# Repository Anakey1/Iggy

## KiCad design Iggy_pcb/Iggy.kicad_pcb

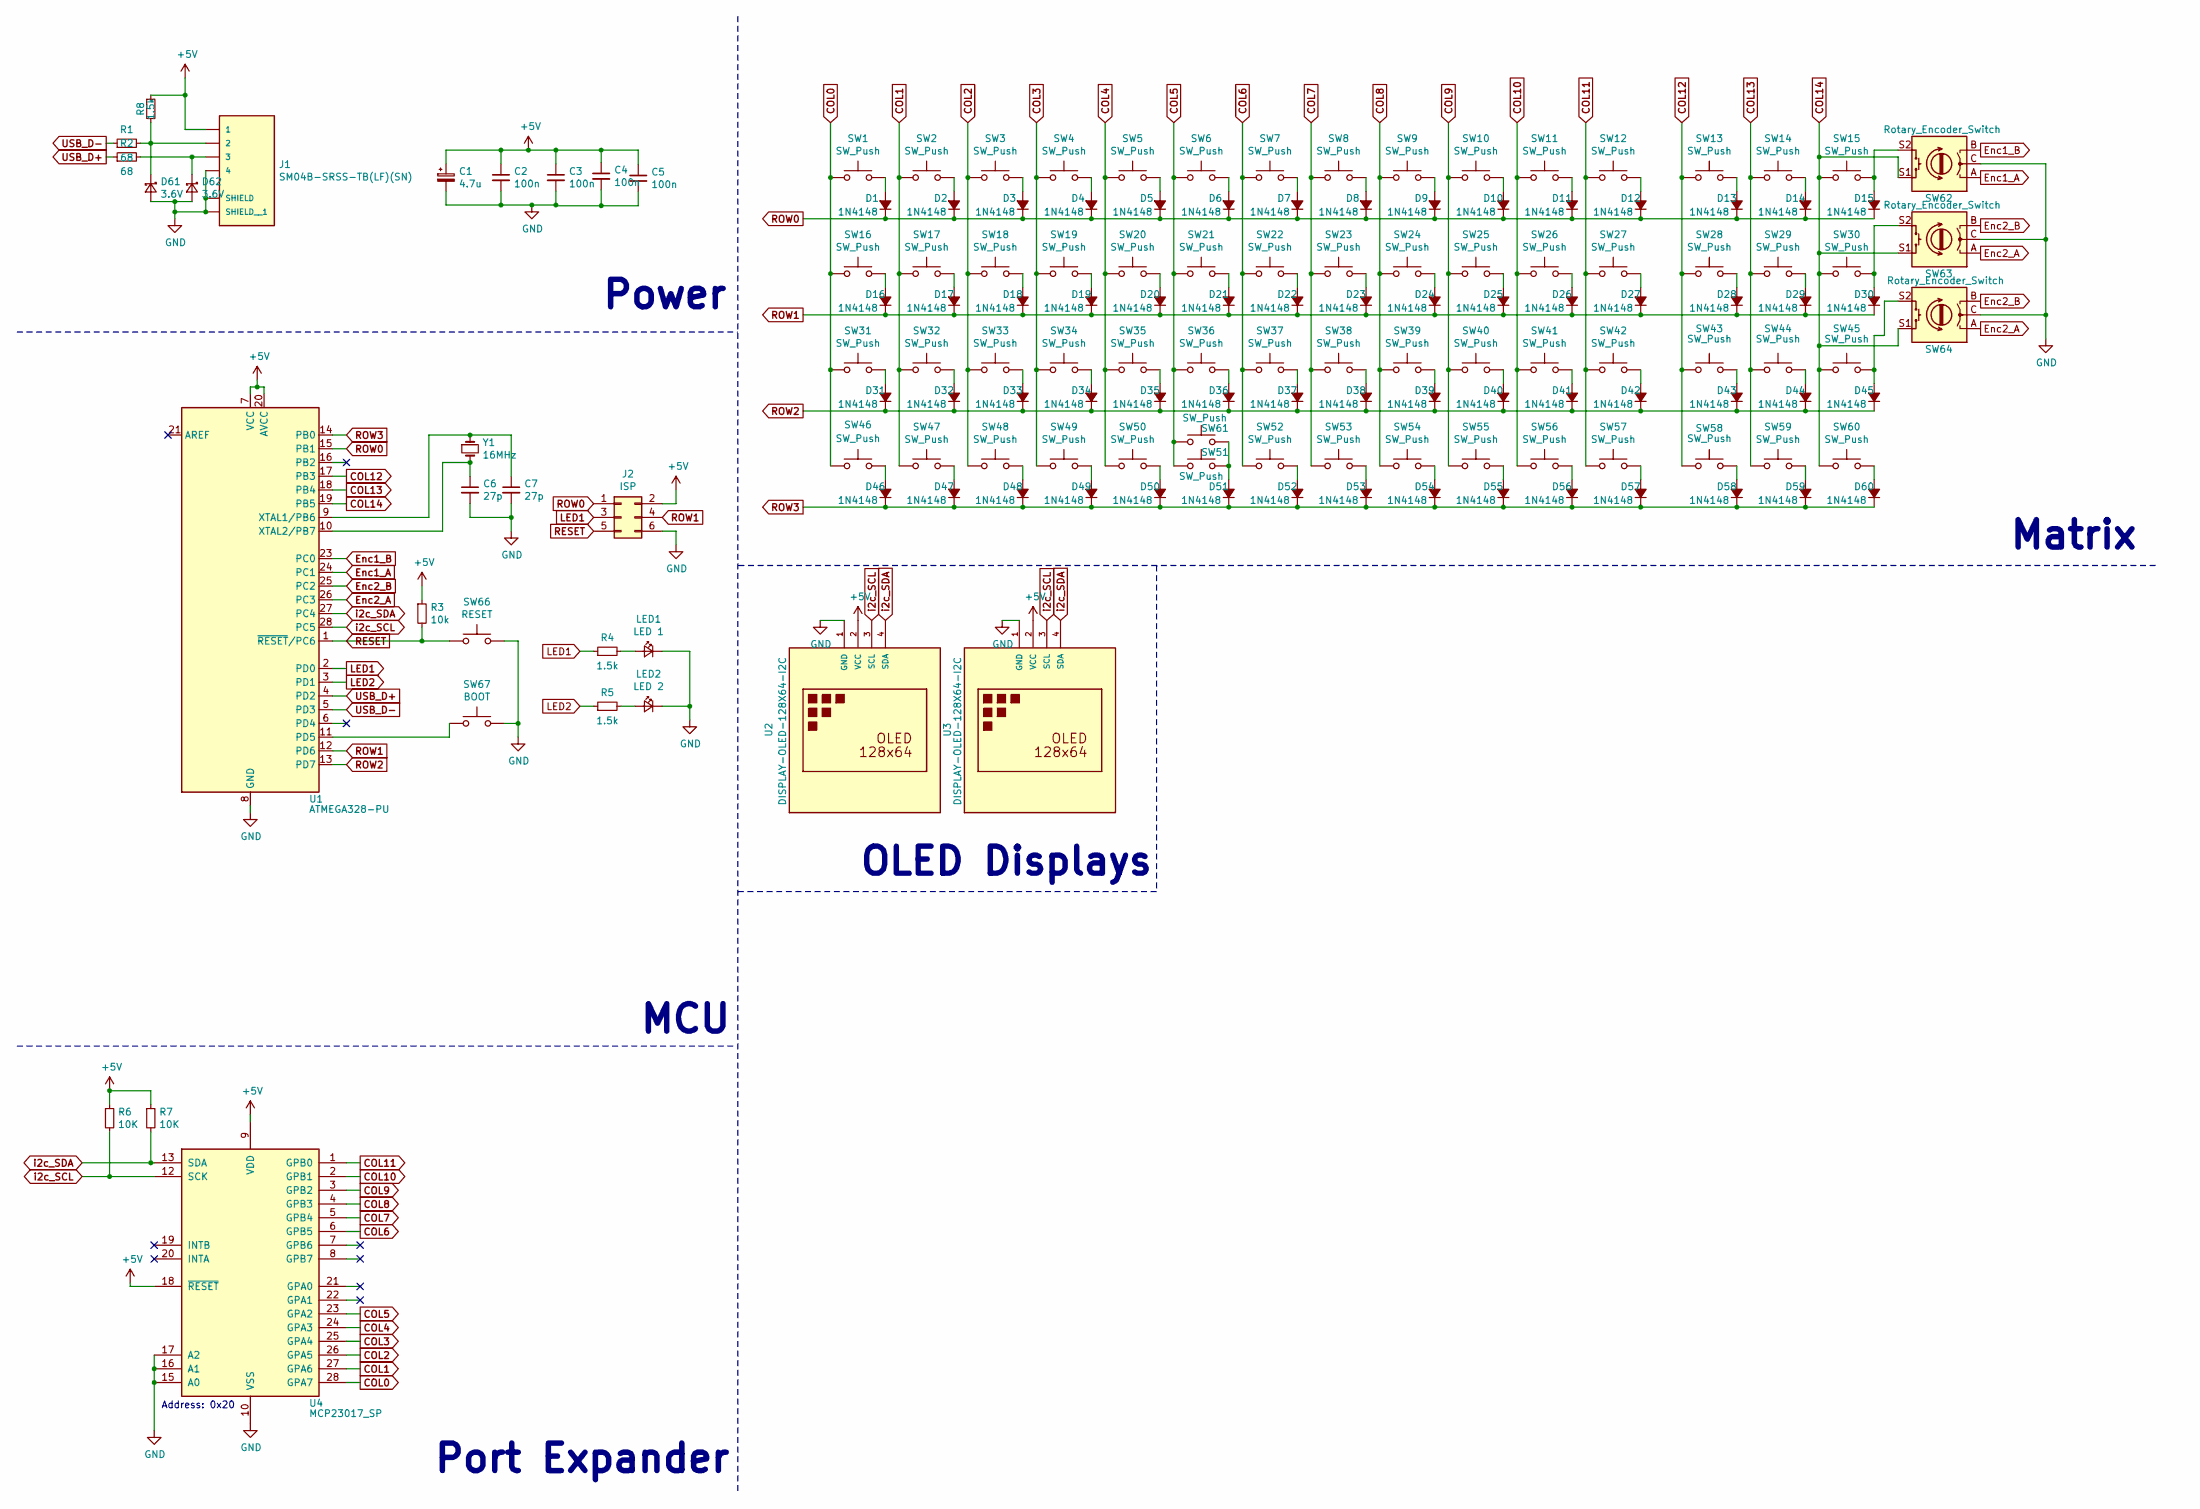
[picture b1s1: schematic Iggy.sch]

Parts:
C1: 4.7u; CP_Radial_D4.0mm_P1.50mm
C2, C3, C4, C5: 100n; C_Disc_D4.3mm_W1.9mm_P5.00mm_no_front
C6, C7: 27p; C_Disc_D4.3mm_W1.9mm_P5.00mm_no_front
D1, D2, D3, D4, D5, D6, D7, D8, D9, D10, D11, D12, D16, D17, D18, D19, D20, D21, D22, D23, D24, D25, D26, D27, D31, D32, D33, D34, D35, D36, D37, D38, D39, D40, D41, D42, D46, D47, D48, D49, D50, D51, D52, D53, D54, D55, D56, D57: 1N4148; D_DO-35_SOD27_P7.62mm_Horizontal_no_front
D13, D14, D15, D28, D29, D30, D43, D44, D45, D58, D59, D60: 1N4148; D_DO-35_SOD27_P7.62mm_Horizontal
D61, D62: 3.6V; D_DO-35_SOD27_P7.62mm_Horizontal
J1: SM04B-SRSS-TB(LF)(SN); JST_SM04B-SRSS-TB(LF)(SN)
J2: ISP; PinHeader_2x03_P2.54mm_Vertical
LED1: LED 1; LED_D3.0mm_Clear
LED2: LED 2; LED_D3.0mm_Clear
R1, R2: 68; R_Axial_DIN0204_L3.6mm_D1.6mm_P5.08mm_Horizontal_no_front
R3: 10k; R_Axial_DIN0204_L3.6mm_D1.6mm_P5.08mm_Horizontal_no_front
R4, R5, R8: 1.5k; R_Axial_DIN0204_L3.6mm_D1.6mm_P5.08mm_Horizontal
R6, R7: 10K; R_Axial_DIN0204_L3.6mm_D1.6mm_P5.08mm_Horizontal_no_front
SW1, SW2, SW3, SW4, SW5, SW6, SW7, SW8, SW9, SW10, SW11, SW12, SW13, SW14, SW15, SW16, SW17, SW18, SW19, SW20, SW21, SW22, SW23, SW24, SW25, SW26, SW27, SW28, SW29, SW30, SW31, SW32, SW33, SW34, SW35, SW36, SW37, SW38, SW39, SW40, SW41, SW42, SW43, SW44, SW45, SW46, SW47, SW48, SW49, SW50, SW51, SW52, SW53, SW54, SW55, SW56, SW57, SW58, SW59, SW60: SW_Push; MX-1U-NoLED
SW61: SW_Push; MX-2U-NoLED
SW62, SW63, SW64: Rotary_Encoder_Switch; RotaryEncoder_Alps_EC11E-Switch_Vertical_H20mm
SW66: RESET; SW_PUSH_6mm
SW67: BOOT; SW_PUSH_6mm
U1: ATMEGA328-PU; DIP-28_W7.62mm_no_front
U2, U3: DISPLAY-OLED-128X64-I2C; DISPLAY-OLED-128X64-I2C-no-lines
U4: MCP23017_SP; DIP-28_W7.62mm_no_front
Y1: 16MHz; Crystal_HC49-4H_Vertical

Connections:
+5V: C1.1, C2.1, C3.1, C4.1, C5.1, J1.1, J2.2, R3.1, R6.1, R7.1, R8.1, U1.7 (VCC), U1.20 (AVCC), U2.2 (VCC), U3.2 (VCC), U4.9 (VDD), U4.18 (~RESET~)
COL0: SW1.2, SW16.2, SW31.2, SW46.2, U4.28 (GPA7)
COL1: SW2.2, SW17.2, SW32.2, SW47.2, U4.27 (GPA6)
COL2: SW3.2, SW18.2, SW33.2, SW48.2, U4.26 (GPA5)
COL3: SW4.2, SW19.2, SW34.2, SW49.2, U4.25 (GPA4)
COL4: SW5.2, SW20.2, SW35.2, SW50.2, U4.24 (GPA3)
COL5: SW6.2, SW21.2, SW36.2, SW51.2, SW61.2, U4.23 (GPA2)
COL6: SW7.2, SW22.2, SW37.2, SW52.2, U4.6 (GPB5)
COL7: SW8.2, SW23.2, SW38.2, SW53.2, U4.5 (GPB4)
COL8: SW9.2, SW24.2, SW39.2, SW54.2, U4.4 (GPB3)
COL9: SW10.2, SW25.2, SW40.2, SW55.2, U4.3 (GPB2)
COL10: SW11.2, SW26.2, SW41.2, SW56.2, U4.2 (GPB1)
COL11: SW12.2, SW27.2, SW42.2, SW57.2, U4.1 (GPB0)
COL12: SW13.2, SW28.2, SW43.2, SW58.2, U1.17 (PB3)
COL13: SW14.2, SW29.2, SW44.2, SW59.2, U1.18 (PB4)
COL14: SW15.2, SW30.2, SW45.2, SW60.2, SW62.S1, SW63.S1, SW64.S1, U1.19 (PB5)
Enc1_A: SW62.A, U1.24 (PC1)
Enc1_B: SW62.B, U1.23 (PC0)
Enc2_A: SW63.A, SW64.A, U1.26 (PC3)
Enc2_B: SW63.B, SW64.B, U1.25 (PC2)
GND: C1.2, C2.2, C3.2, C4.2, C5.2, C6.2, C7.2, D61.2 (A), D62.2 (A), J1.4, J1.S1 (SHIELD), J1.S2 (SHIELD__1), J2.6, LED1.1 (K), LED2.1 (K), SW62.C, SW63.C, SW64.C, SW66.2, SW67.2, U1.8 (GND), U1.22 (GND), U2.1 (GND), U3.1 (GND), U4.10 (VSS), U4.15 (A0), U4.16 (A1), U4.17 (A2)
LED1: J2.3, R4.1, U1.2 (PD0)
LED2: R5.1, U1.3 (PD1)
unnamed: C6.1, U1.10 (XTAL2/PB7), Y1.2
unnamed: C7.1, U1.9 (XTAL1/PB6), Y1.1
unnamed: D1.2 (A), SW1.1
unnamed: D2.2 (A), SW2.1
unnamed: D3.2 (A), SW3.1
unnamed: D4.2 (A), SW4.1
unnamed: D5.2 (A), SW5.1
unnamed: D6.2 (A), SW6.1
unnamed: D7.2 (A), SW7.1
unnamed: D8.2 (A), SW8.1
unnamed: D9.2 (A), SW9.1
unnamed: D10.2 (A), SW10.1
unnamed: D11.2 (A), SW11.1
unnamed: D12.2 (A), SW12.1
unnamed: D13.2 (A), SW13.1
unnamed: D14.2 (A), SW14.1
unnamed: D15.2 (A), SW15.1, SW62.S2
unnamed: D16.2 (A), SW16.1
unnamed: D17.2 (A), SW17.1
unnamed: D18.2 (A), SW18.1
unnamed: D19.2 (A), SW19.1
unnamed: D20.2 (A), SW20.1
unnamed: D21.2 (A), SW21.1
unnamed: D22.2 (A), SW22.1
unnamed: D23.2 (A), SW23.1
unnamed: D24.2 (A), SW24.1
unnamed: D25.2 (A), SW25.1
unnamed: D26.2 (A), SW26.1
unnamed: D27.2 (A), SW27.1
unnamed: D28.2 (A), SW28.1
unnamed: D29.2 (A), SW29.1
unnamed: D30.2 (A), SW30.1, SW63.S2
unnamed: D31.2 (A), SW31.1
unnamed: D32.2 (A), SW32.1
unnamed: D33.2 (A), SW33.1
unnamed: D34.2 (A), SW34.1
unnamed: D35.2 (A), SW35.1
unnamed: D36.2 (A), SW36.1
unnamed: D37.2 (A), SW37.1
unnamed: D38.2 (A), SW38.1
unnamed: D39.2 (A), SW39.1
unnamed: D40.2 (A), SW40.1
unnamed: D41.2 (A), SW41.1
unnamed: D42.2 (A), SW42.1
unnamed: D43.2 (A), SW43.1
unnamed: D44.2 (A), SW44.1
unnamed: D45.2 (A), SW45.1, SW64.S2
unnamed: D46.2 (A), SW46.1
unnamed: D47.2 (A), SW47.1
unnamed: D48.2 (A), SW48.1
unnamed: D49.2 (A), SW49.1
unnamed: D50.2 (A), SW50.1
unnamed: D51.2 (A), SW51.1, SW61.1
unnamed: D52.2 (A), SW52.1
unnamed: D53.2 (A), SW53.1
unnamed: D54.2 (A), SW54.1
unnamed: D55.2 (A), SW55.1
unnamed: D56.2 (A), SW56.1
unnamed: D57.2 (A), SW57.1
unnamed: D58.2 (A), SW58.1
unnamed: D59.2 (A), SW59.1
unnamed: D60.2 (A), SW60.1
unnamed: D61.1 (K), J1.2, R1.2, R8.2
unnamed: D62.1 (K), J1.3, R2.2
unnamed: LED1.2 (A), R4.2
unnamed: LED2.2 (A), R5.2
unnamed: SW67.1, U1.11 (PD5)
RESET: J2.5, R3.2, SW66.1, U1.1 (~RESET~/PC6)
ROW0: D1.1 (K), D2.1 (K), D3.1 (K), D4.1 (K), D5.1 (K), D6.1 (K), D7.1 (K), D8.1 (K), D9.1 (K), D10.1 (K), D11.1 (K), D12.1 (K), D13.1 (K), D14.1 (K), D15.1 (K), J2.1, U1.15 (PB1)
ROW1: D16.1 (K), D17.1 (K), D18.1 (K), D19.1 (K), D20.1 (K), D21.1 (K), D22.1 (K), D23.1 (K), D24.1 (K), D25.1 (K), D26.1 (K), D27.1 (K), D28.1 (K), D29.1 (K), D30.1 (K), J2.4, U1.12 (PD6)
ROW2: D31.1 (K), D32.1 (K), D33.1 (K), D34.1 (K), D35.1 (K), D36.1 (K), D37.1 (K), D38.1 (K), D39.1 (K), D40.1 (K), D41.1 (K), D42.1 (K), D43.1 (K), D44.1 (K), D45.1 (K), U1.13 (PD7)
ROW3: D46.1 (K), D47.1 (K), D48.1 (K), D49.1 (K), D50.1 (K), D51.1 (K), D52.1 (K), D53.1 (K), D54.1 (K), D55.1 (K), D56.1 (K), D57.1 (K), D58.1 (K), D59.1 (K), D60.1 (K), U1.14 (PB0)
USB_D+: R2.1, U1.4 (PD2)
USB_D-: R1.1, U1.5 (PD3)
i2c_SCL: R6.2, U1.28 (PC5), U2.3 (SCL), U3.3 (SCL), U4.12 (SCK)
i2c_SDA: R7.2, U1.27 (PC4), U2.4 (SDA), U3.4 (SDA), U4.13 (SDA)

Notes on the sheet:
Power
Matrix
MCU
Port Expander
Address: 0x20
OLED Displays

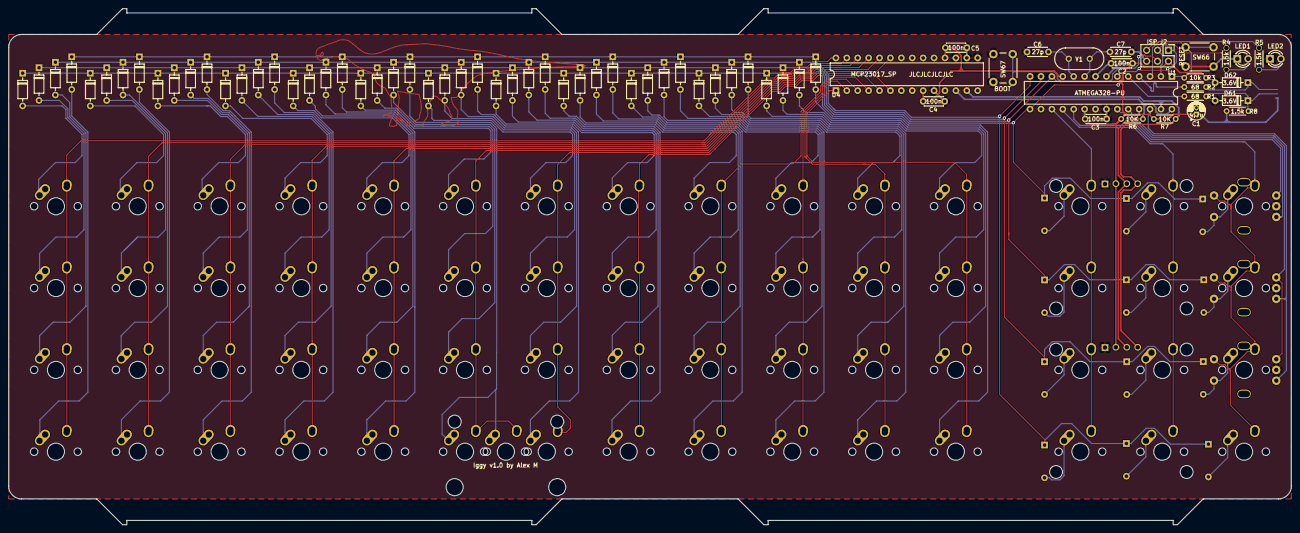
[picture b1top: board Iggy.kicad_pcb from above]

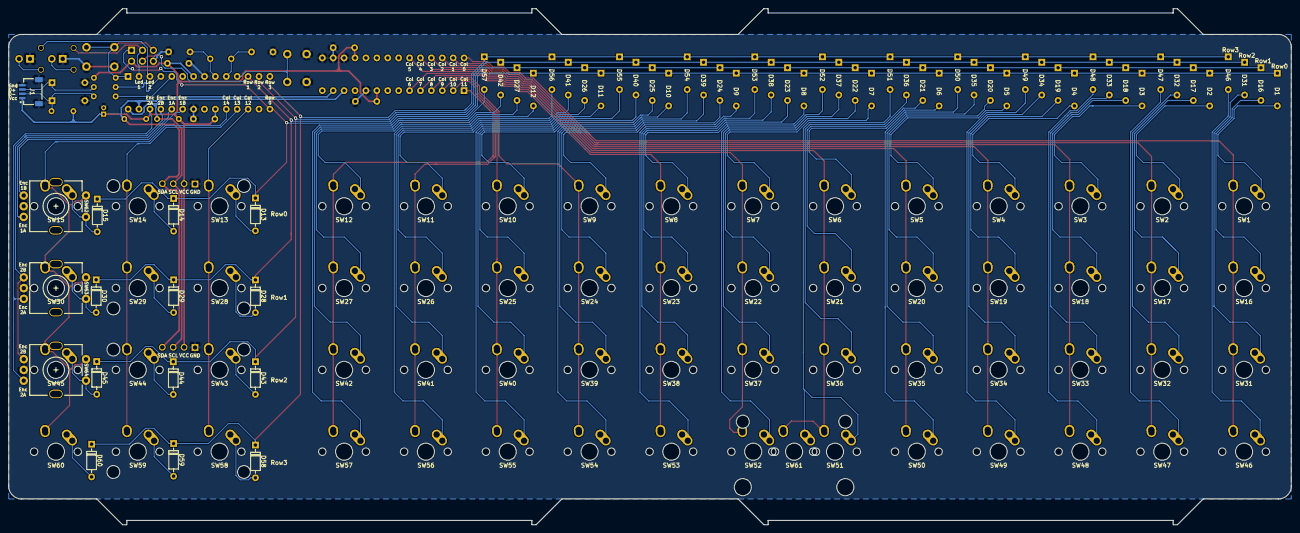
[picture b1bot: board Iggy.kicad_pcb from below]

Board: 2 copper layers, 298.6 x 120.2 mm, 152 parts (13 on the bottom side), 99 nets.

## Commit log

2021-01-15 cleared up libraries, pcb done
